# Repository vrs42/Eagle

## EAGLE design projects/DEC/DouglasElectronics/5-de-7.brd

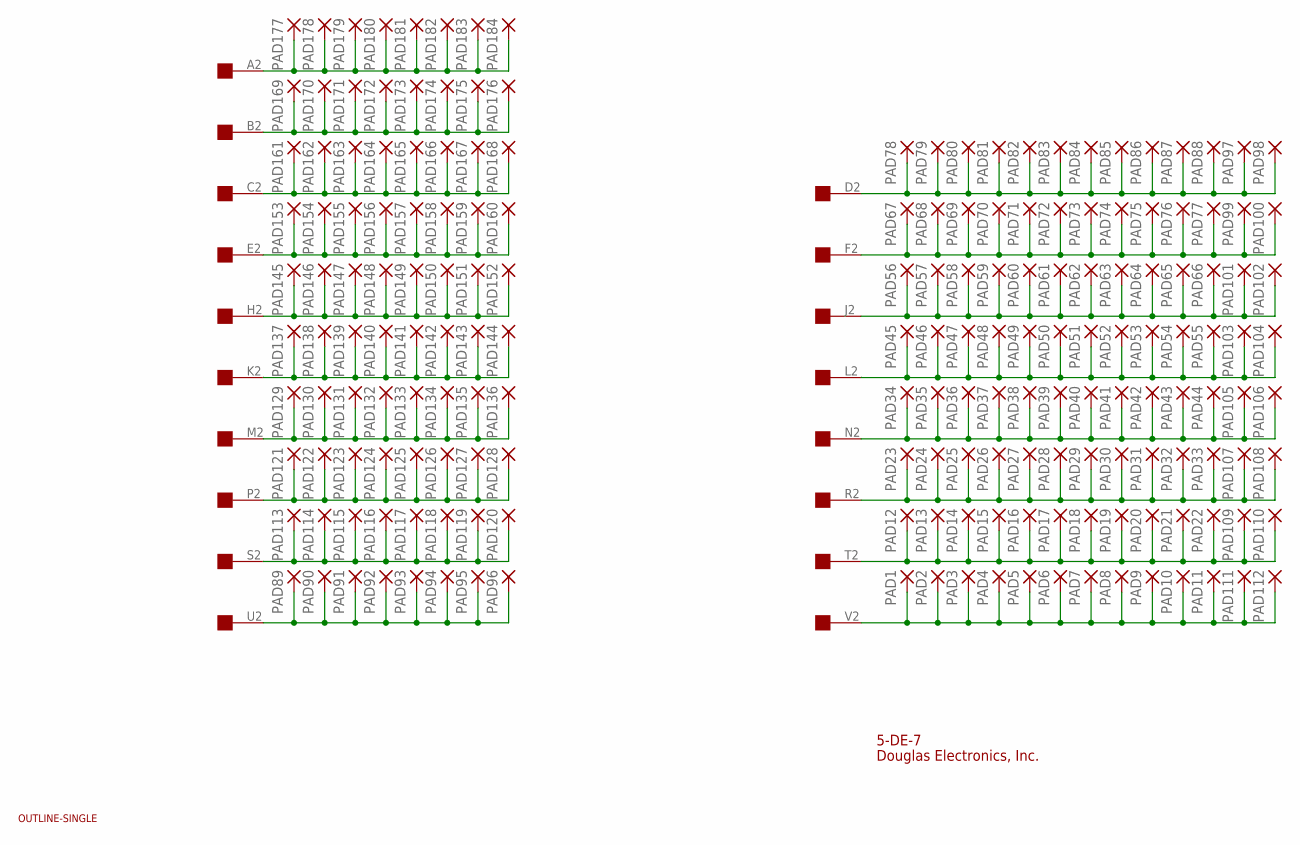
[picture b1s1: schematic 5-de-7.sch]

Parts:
PAD1, PAD2, PAD3, PAD4, PAD5, PAD6, PAD7, PAD8, PAD9, PAD10, PAD11, PAD12, PAD13, PAD14, PAD15, PAD16, PAD17, PAD18, PAD19, PAD20, PAD21, PAD22, PAD23, PAD24, PAD25, PAD26, PAD27, PAD28, PAD29, PAD30, PAD31, PAD32, PAD33, PAD34, PAD35, PAD36, PAD37, PAD38, PAD39, PAD40, PAD41, PAD42, PAD43, PAD44, PAD45, PAD46, PAD47, PAD48, PAD49, PAD50, PAD51, PAD52, PAD53, PAD54, PAD55, PAD56, PAD57, PAD58, PAD59, PAD60, PAD61, PAD62, PAD63, PAD64, PAD65, PAD66, PAD67, PAD68, PAD69, PAD70, PAD71, PAD72, PAD73, PAD74, PAD75, PAD76, PAD77, PAD78, PAD79, PAD80, PAD81, PAD82, PAD83, PAD84, PAD85, PAD86, PAD87, PAD88, PAD89, PAD90, PAD91, PAD92, PAD93, PAD94, PAD95, PAD96, PAD97, PAD98, PAD99, PAD100, PAD101, PAD102, PAD103, PAD104, PAD105, PAD106, PAD107, PAD108, PAD109, PAD110, PAD111, PAD112, PAD113, PAD114, PAD115, PAD116, PAD117, PAD118, PAD119, PAD120, PAD121, PAD122, PAD123, PAD124, PAD125, PAD126, PAD127, PAD128, PAD129, PAD130, PAD131, PAD132, PAD133, PAD134, PAD135, PAD136, PAD137, PAD138, PAD139, PAD140, PAD141, PAD142, PAD143, PAD144, PAD145, PAD146, PAD147, PAD148, PAD149, PAD150, PAD151, PAD152, PAD153, PAD154, PAD155, PAD156, PAD157, PAD158, PAD159, PAD160, PAD161, PAD162, PAD163, PAD164, PAD165, PAD166, PAD167, PAD168, PAD169, PAD170, PAD171, PAD172, PAD173, PAD174, PAD175, PAD176, PAD177, PAD178, PAD179, PAD180, PAD181, PAD182, PAD183, PAD184: 2,54/1,1
U$2: OUTLINE-SINGLE; SINGLE
U$3: EDGE-1; EDGE-CON1

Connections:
A: PAD177.1, PAD178.1, PAD179.1, PAD180.1, PAD181.1, PAD182.1, PAD183.1, PAD184.1, U$3.A2
B: PAD169.1, PAD170.1, PAD171.1, PAD172.1, PAD173.1, PAD174.1, PAD175.1, PAD176.1, U$3.B2
C: PAD161.1, PAD162.1, PAD163.1, PAD164.1, PAD165.1, PAD166.1, PAD167.1, PAD168.1, U$3.C2
D: PAD78.1, PAD79.1, PAD80.1, PAD81.1, PAD82.1, PAD83.1, PAD84.1, PAD85.1, PAD86.1, PAD87.1, PAD88.1, PAD97.1, PAD98.1, U$3.D2
E: PAD153.1, PAD154.1, PAD155.1, PAD156.1, PAD157.1, PAD158.1, PAD159.1, PAD160.1, U$3.E2
F: PAD67.1, PAD68.1, PAD69.1, PAD70.1, PAD71.1, PAD72.1, PAD73.1, PAD74.1, PAD75.1, PAD76.1, PAD77.1, PAD99.1, PAD100.1, U$3.F2
H: PAD145.1, PAD146.1, PAD147.1, PAD148.1, PAD149.1, PAD150.1, PAD151.1, PAD152.1, U$3.H2
J: PAD56.1, PAD57.1, PAD58.1, PAD59.1, PAD60.1, PAD61.1, PAD62.1, PAD63.1, PAD64.1, PAD65.1, PAD66.1, PAD101.1, PAD102.1, U$3.J2
K: PAD137.1, PAD138.1, PAD139.1, PAD140.1, PAD141.1, PAD142.1, PAD143.1, PAD144.1, U$3.K2
L: PAD45.1, PAD46.1, PAD47.1, PAD48.1, PAD49.1, PAD50.1, PAD51.1, PAD52.1, PAD53.1, PAD54.1, PAD55.1, PAD103.1, PAD104.1, U$3.L2
M: PAD129.1, PAD130.1, PAD131.1, PAD132.1, PAD133.1, PAD134.1, PAD135.1, PAD136.1, U$3.M2
N: PAD34.1, PAD35.1, PAD36.1, PAD37.1, PAD38.1, PAD39.1, PAD40.1, PAD41.1, PAD42.1, PAD43.1, PAD44.1, PAD105.1, PAD106.1, U$3.N2
P: PAD121.1, PAD122.1, PAD123.1, PAD124.1, PAD125.1, PAD126.1, PAD127.1, PAD128.1, U$3.P2
R: PAD23.1, PAD24.1, PAD25.1, PAD26.1, PAD27.1, PAD28.1, PAD29.1, PAD30.1, PAD31.1, PAD32.1, PAD33.1, PAD107.1, PAD108.1, U$3.R2
S: PAD113.1, PAD114.1, PAD115.1, PAD116.1, PAD117.1, PAD118.1, PAD119.1, PAD120.1, U$3.S2
T: PAD12.1, PAD13.1, PAD14.1, PAD15.1, PAD16.1, PAD17.1, PAD18.1, PAD19.1, PAD20.1, PAD21.1, PAD22.1, PAD109.1, PAD110.1, U$3.T2
U: PAD89.1, PAD90.1, PAD91.1, PAD92.1, PAD93.1, PAD94.1, PAD95.1, PAD96.1, U$3.U2
V: PAD1.1, PAD2.1, PAD3.1, PAD4.1, PAD5.1, PAD6.1, PAD7.1, PAD8.1, PAD9.1, PAD10.1, PAD11.1, PAD111.1, PAD112.1, U$3.V2

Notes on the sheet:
5-DE-7
Douglas Electronics, Inc.

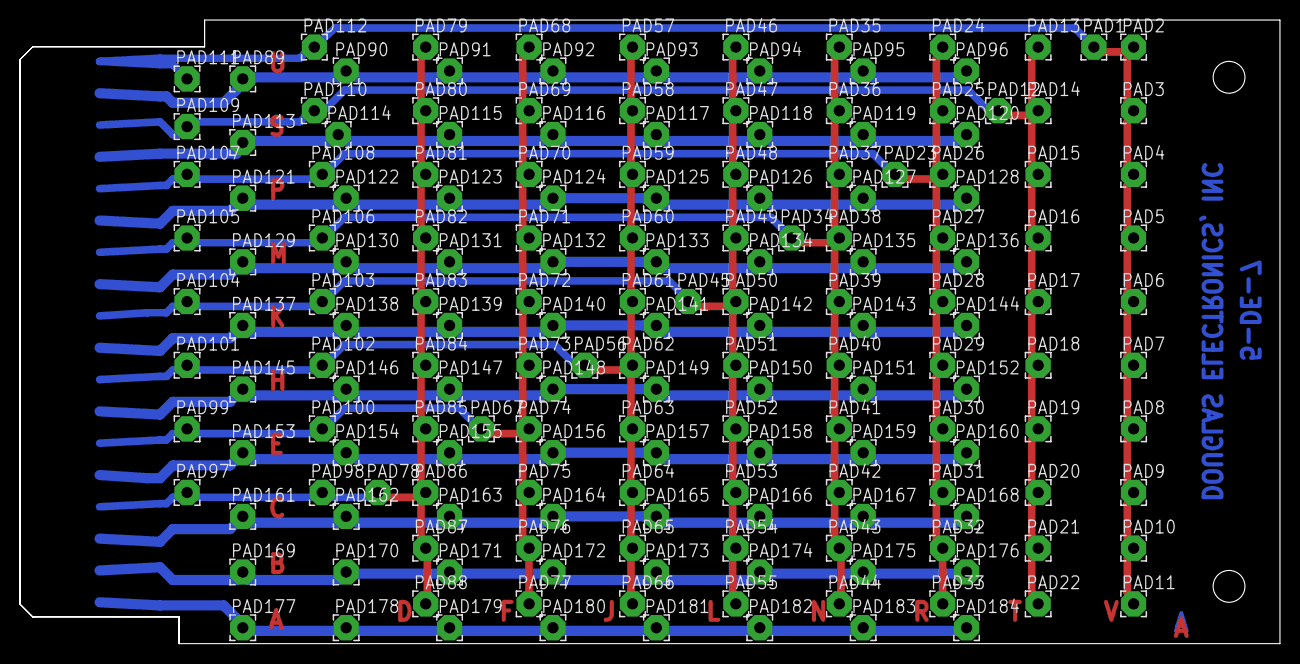
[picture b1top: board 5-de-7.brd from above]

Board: 2 copper layers, 125.7 x 62.2 mm, 186 parts (0 on the bottom side), 18 nets.

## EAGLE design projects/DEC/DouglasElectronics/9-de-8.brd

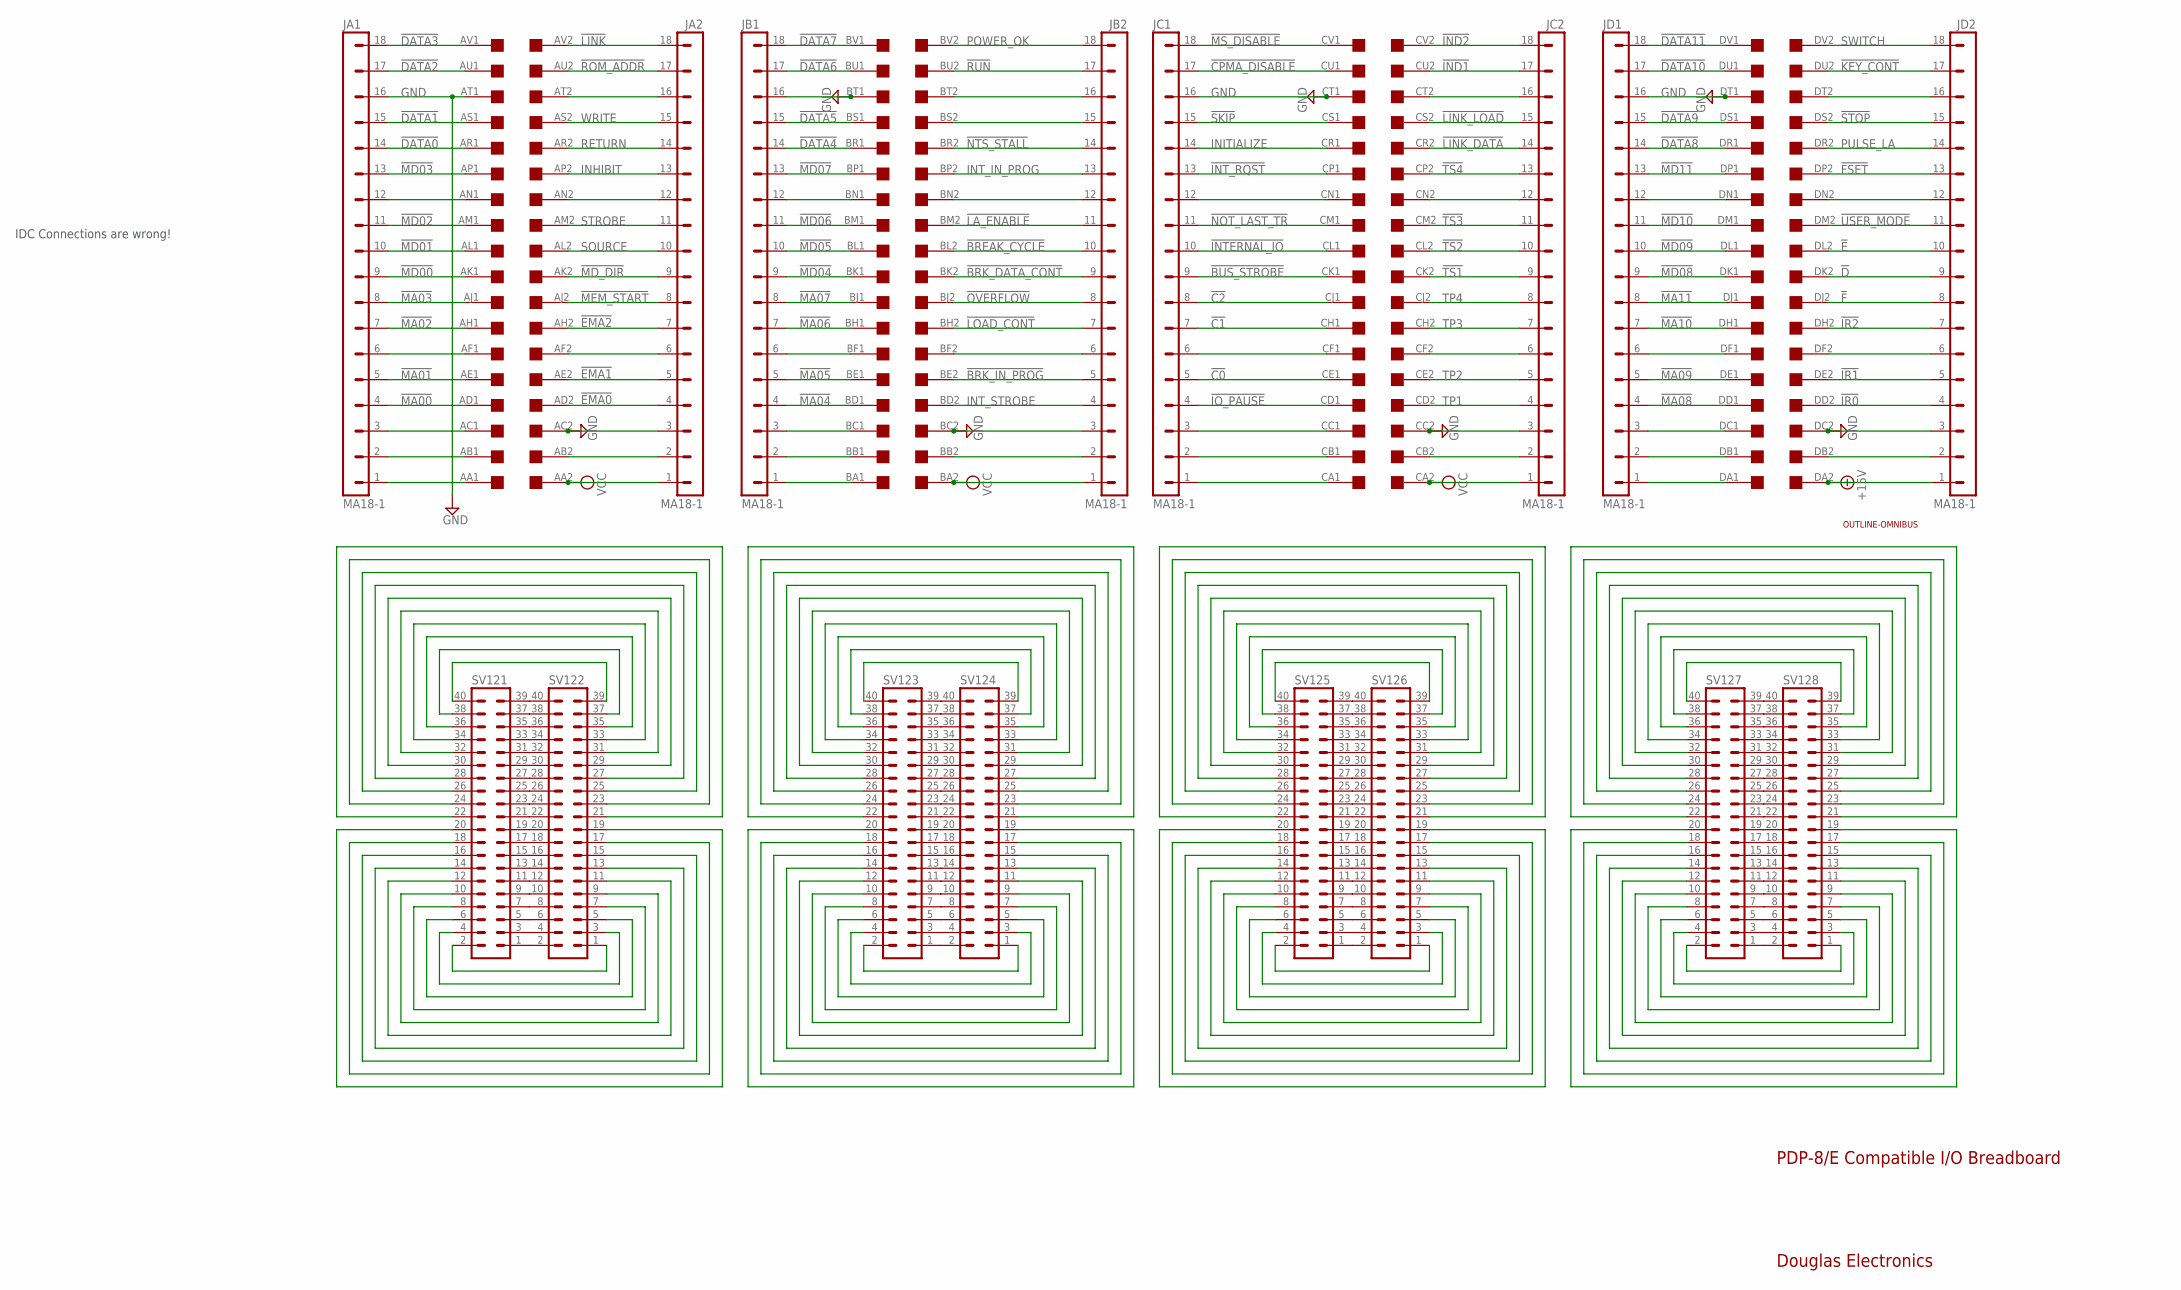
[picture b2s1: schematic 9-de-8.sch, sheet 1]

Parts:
JA1, JA2: MA18-1
JB1, JB2: MA18-1
JC1, JC2: MA18-1
JD1, JD2: MA18-1
SV121, SV122, SV123, SV124, SV125, SV126, SV127, SV128: MA20-2
U$1: OUTLINE-OMNIBUS; OMNIBUS
U$2: QUAD; EDGE-CON8

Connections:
!BREAK_CYCLE: JB2.10, U$2.BL2
!BRK_DATA_CONT: JB2.9, U$2.BK2
!BRK_IN_PROG: JB2.5, U$2.BE2
!BUS_STROBE: JC1.9, U$2.CK1
!C0: JC1.5, U$2.CE1
!C1: JC1.7, U$2.CH1
!C2: JC1.8, U$2.CJ1
!CPMA_DISABLE: JC1.17, U$2.CU1
!D: JD2.9, U$2.DK2
!DATA0: JA1.14, U$2.AR1
!DATA1: JA1.15, U$2.AS1
!DATA2: JA1.17, U$2.AU1
!DATA3: JA1.18, U$2.AV1
!DATA4: JB1.14, U$2.BR1
!DATA5: JB1.15, U$2.BS1
!DATA6: JB1.17, U$2.BU1
!DATA7: JB1.18, U$2.BV1
!DATA8: JD1.14, U$2.DR1
!DATA9: JD1.15, U$2.DS1
!DATA10: JD1.17, U$2.DU1
!DATA11: JD1.18, U$2.DV1
!E: JD2.10, U$2.DL2
!EMA0: JA2.4, U$2.AD2
!EMA1: JA2.5, U$2.AE2
!EMA2: JA2.7, U$2.AH2
!F: JD2.8, U$2.DJ2
!FSET: JD2.13, U$2.DP2
!IND1: JC2.17, U$2.CU2
!IND2: JC2.18, U$2.CV2
!INTERNAL_IO: JC1.10, U$2.CL1
!INT_RQST: JC1.13, U$2.CP1
!IO_PAUSE: JC1.4, U$2.CD1
!IR0: JD2.4, U$2.DD2
!IR1: JD2.5, U$2.DE2
!IR2: JD2.7, U$2.DH2
!KEY_CONT: JD2.17, U$2.DU2
!LA_ENABLE: JB2.11, U$2.BM2
!LINK: JA2.18, U$2.AV2
!LINK_DATA: JC2.14, U$2.CR2
!LINK_LOAD: JC2.15, U$2.CS2
!LOAD_CONT: JB2.7, U$2.BH2
!MA00: JA1.4, U$2.AD1
!MA01: JA1.5, U$2.AE1
!MA02: JA1.7, U$2.AH1
!MA03: JA1.8, U$2.AJ1
!MA04: JB1.4, U$2.BD1
!MA05: JB1.5, U$2.BE1
!MA06: JB1.7, U$2.BH1
!MA07: JB1.8, U$2.BJ1
!MA08: JD1.4, U$2.DD1
!MA09: JD1.5, U$2.DE1
!MA10: JD1.7, U$2.DH1
!MA11: JD1.8, U$2.DJ1
!MD00: JA1.9, U$2.AK1
!MD01: JA1.10, U$2.AL1
!MD02: JA1.11, U$2.AM1
!MD03: JA1.13, U$2.AP1
!MD04: JB1.9, U$2.BK1
!MD05: JB1.10, U$2.BL1
!MD06: JB1.11, U$2.BM1
!MD07: JB1.13, U$2.BP1
!MD08: JD1.9, U$2.DK1
!MD09: JD1.10, U$2.DL1
!MD10: JD1.11, U$2.DM1
!MD11: JD1.13, U$2.DP1
!MD_DIR: JA2.9, U$2.AK2
!MEM_START: JA2.8, U$2.AJ2
!MS_DISABLE: JC1.18, U$2.CV1
!NOT_LAST_TR: JC1.11, U$2.CM1
!NTS_STALL: JB2.14, U$2.BR2
!OVERFLOW: JB2.8, U$2.BJ2
!ROM_ADDR: JA2.17, U$2.AU2
!RUN: JB2.17, U$2.BU2
!SKIP: JC1.15, U$2.CS1
!STOP: JD2.15, U$2.DS2
!TS1: JC2.9, U$2.CK2
!TS2: JC2.10, U$2.CL2
!TS3: JC2.11, U$2.CM2
!TS4: JC2.13, U$2.CP2
!USER_MODE: JD2.11, U$2.DM2
+15V: JD2.1, U$2.DA2
GND: JA1.16, JA2.3, JB1.16, JB2.3, JC1.16, JC2.3, JD1.16, JD2.3, U$2.AC2, U$2.AT1, U$2.BC2, U$2.BT1, U$2.CC2, U$2.CT1, U$2.DC2, U$2.DT1; also elsewhere on the board
INHIBIT: JA2.13, U$2.AP2
INITIALIZE: JC1.14, U$2.CR1
INT_IN_PROG: JB2.13, U$2.BP2
INT_STROBE: JB2.4, U$2.BD2
unnamed: JA1.2, U$2.AB1
unnamed: JA1.1, U$2.AA1
unnamed: JB1.2, U$2.BB1
unnamed: JB1.1, U$2.BA1
unnamed: JC1.1, U$2.CA1
unnamed: JB2.15, U$2.BS2
unnamed: JC1.2, U$2.CB1
unnamed: JD1.1, U$2.DA1
unnamed: JD1.2, U$2.DB1
unnamed: SV121.1, SV122.2
unnamed: SV121.3, SV122.4
unnamed: SV121.5, SV122.6
unnamed: SV121.7, SV122.8
unnamed: SV121.9, SV122.10
unnamed: SV121.11, SV122.12
unnamed: SV121.13, SV122.14
unnamed: SV121.15, SV122.16
unnamed: SV121.17, SV122.18
unnamed: SV121.19, SV122.20
unnamed: SV121.21, SV122.22
unnamed: SV121.23, SV122.24
unnamed: SV121.25, SV122.26
unnamed: SV121.27, SV122.28
unnamed: SV121.29, SV122.30
unnamed: SV121.31, SV122.32
unnamed: SV121.33, SV122.34
unnamed: SV121.35, SV122.36
unnamed: SV121.37, SV122.38
unnamed: SV121.39, SV122.40
unnamed: SV123.1, SV124.2
unnamed: SV123.3, SV124.4
unnamed: SV123.5, SV124.6
unnamed: SV123.7, SV124.8
unnamed: SV123.9, SV124.10
unnamed: SV123.11, SV124.12
unnamed: SV123.13, SV124.14
unnamed: SV123.15, SV124.16
unnamed: SV123.17, SV124.18
unnamed: SV123.19, SV124.20
unnamed: SV123.21, SV124.22
unnamed: SV123.23, SV124.24
unnamed: SV123.25, SV124.26
unnamed: SV123.27, SV124.28
unnamed: SV123.29, SV124.30
unnamed: SV123.31, SV124.32
unnamed: SV123.33, SV124.34
unnamed: SV123.35, SV124.36
unnamed: SV123.37, SV124.38
unnamed: SV123.39, SV124.40
unnamed: SV123.40, SV124.39
unnamed: SV123.38, SV124.37
unnamed: SV123.36, SV124.35
unnamed: SV123.34, SV124.33
unnamed: SV123.32, SV124.31
unnamed: SV123.2, SV124.1
unnamed: SV123.4, SV124.3
unnamed: SV123.6, SV124.5
unnamed: SV123.8, SV124.7
unnamed: SV123.10, SV124.9
unnamed: SV123.12, SV124.11
unnamed: SV123.30, SV124.29
unnamed: SV123.14, SV124.13
unnamed: SV123.18, SV124.17
unnamed: SV123.20, SV124.19
unnamed: SV123.22, SV124.21
unnamed: SV123.24, SV124.23
unnamed: SV123.26, SV124.25
unnamed: SV123.28, SV124.27
unnamed: SV123.16, SV124.15
unnamed: SV125.1, SV126.2
unnamed: SV125.3, SV126.4
unnamed: SV125.5, SV126.6
unnamed: SV125.7, SV126.8
unnamed: SV125.9, SV126.10
unnamed: SV125.11, SV126.12
unnamed: SV125.13, SV126.14
unnamed: SV125.15, SV126.16
unnamed: SV125.17, SV126.18
unnamed: SV125.19, SV126.20
unnamed: SV125.21, SV126.22
unnamed: SV125.23, SV126.24
unnamed: SV125.25, SV126.26
unnamed: SV125.27, SV126.28
unnamed: SV125.29, SV126.30
unnamed: SV125.31, SV126.32
unnamed: SV125.33, SV126.34
unnamed: SV125.35, SV126.36
unnamed: SV125.37, SV126.38
unnamed: SV125.39, SV126.40
unnamed: SV121.40, SV122.39
unnamed: SV121.38, SV122.37
unnamed: SV121.36, SV122.35
unnamed: SV121.34, SV122.33
unnamed: SV121.32, SV122.31
unnamed: SV121.2, SV122.1
unnamed: SV121.4, SV122.3
unnamed: SV121.6, SV122.5
unnamed: SV121.8, SV122.7
unnamed: SV121.10, SV122.9
unnamed: SV121.12, SV122.11
unnamed: SV121.30, SV122.29
unnamed: SV121.14, SV122.13
unnamed: SV121.16, SV122.15
unnamed: SV121.18, SV122.17
unnamed: SV121.20, SV122.19
unnamed: SV121.22, SV122.21
unnamed: SV121.24, SV122.23
unnamed: SV121.26, SV122.25
unnamed: SV121.28, SV122.27
unnamed: SV125.40, SV126.39
unnamed: SV125.38, SV126.37
unnamed: SV125.36, SV126.35
unnamed: SV125.34, SV126.33
unnamed: SV125.32, SV126.31
unnamed: SV125.2, SV126.1
unnamed: SV125.4, SV126.3
unnamed: SV125.6, SV126.5
unnamed: SV125.8, SV126.7
unnamed: SV125.10, SV126.9
unnamed: SV125.12, SV126.11
unnamed: SV125.30, SV126.29
unnamed: SV125.14, SV126.13
unnamed: SV125.18, SV126.17
unnamed: SV125.20, SV126.19
unnamed: SV125.22, SV126.21
unnamed: SV125.24, SV126.23
unnamed: SV125.26, SV126.25
unnamed: SV125.28, SV126.27
unnamed: SV125.16, SV126.15
unnamed: SV127.1, SV128.2
unnamed: SV127.3, SV128.4
unnamed: SV127.5, SV128.6
unnamed: SV127.7, SV128.8
unnamed: SV127.9, SV128.10
unnamed: SV127.11, SV128.12
unnamed: SV127.13, SV128.14
unnamed: SV127.15, SV128.16
unnamed: SV127.17, SV128.18
unnamed: SV127.19, SV128.20
unnamed: SV127.21, SV128.22
unnamed: SV127.23, SV128.24
unnamed: SV127.25, SV128.26
unnamed: SV127.27, SV128.28
unnamed: SV127.29, SV128.30
unnamed: SV127.31, SV128.32
unnamed: SV127.33, SV128.34
unnamed: SV127.35, SV128.36
unnamed: SV127.37, SV128.38
unnamed: SV127.39, SV128.40
unnamed: SV127.40, SV128.39
unnamed: SV127.38, SV128.37
unnamed: SV127.36, SV128.35
unnamed: SV127.34, SV128.33
unnamed: SV127.32, SV128.31
unnamed: SV127.2, SV128.1
unnamed: SV127.4, SV128.3
unnamed: SV127.6, SV128.5
unnamed: SV127.8, SV128.7
unnamed: SV127.10, SV128.9
unnamed: SV127.12, SV128.11
unnamed: SV127.30, SV128.29
unnamed: SV127.14, SV128.13
unnamed: SV127.18, SV128.17
unnamed: SV127.20, SV128.19
unnamed: SV127.22, SV128.21
unnamed: SV127.24, SV128.23
unnamed: SV127.26, SV128.25
unnamed: SV127.28, SV128.27
unnamed: SV127.16, SV128.15
unnamed: JA2.6, U$2.AF2
unnamed: JB1.6, U$2.BF1
unnamed: JB2.6, U$2.BF2
unnamed: JC1.6, U$2.CF1
unnamed: JC2.6, U$2.CF2
unnamed: JD1.6, U$2.DF1
unnamed: JD2.6, U$2.DF2
unnamed: JD2.12, U$2.DN2
unnamed: JD1.12, U$2.DN1
unnamed: JC2.12, U$2.CN2
unnamed: JC1.12, U$2.CN1
unnamed: JB1.12, U$2.BN1
unnamed: JB2.12, U$2.BN2
unnamed: JA1.6, U$2.AF1
unnamed: JA1.12, U$2.AN1
unnamed: JA2.12, U$2.AN2
unnamed: JA2.16, U$2.AT2
unnamed: JB2.16, U$2.BT2
unnamed: JC2.16, U$2.CT2
unnamed: JD2.16, U$2.DT2
unnamed: JA1.3, U$2.AC1
unnamed: JB1.3, U$2.BC1
unnamed: JC1.3, U$2.CC1
unnamed: JD1.3, U$2.DC1
unnamed: JA2.2, U$2.AB2
unnamed: JB2.2, U$2.BB2
unnamed: JC2.2, U$2.CB2
unnamed: JD2.2, U$2.DB2
POWER_OK: JB2.18, U$2.BV2
PULSE_LA: JD2.14, U$2.DR2
RETURN: JA2.14, U$2.AR2
SOURCE: JA2.10, U$2.AL2
STROBE: JA2.11, U$2.AM2
SWITCH: JD2.18, U$2.DV2
TP1: JC2.4, U$2.CD2
TP2: JC2.5, U$2.CE2
TP3: JC2.7, U$2.CH2
TP4: JC2.8, U$2.CJ2
VCC: JA2.1, JB2.1, JC2.1, U$2.AA2, U$2.BA2, U$2.CA2; also elsewhere on the board
WRITE: JA2.15, U$2.AS2

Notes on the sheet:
PDP-8/E Compatible I/O Breadboard
Douglas Electronics
IDC Connections are wrong!
